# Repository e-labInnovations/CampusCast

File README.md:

<p align="center">
  
</p>

<p align="justify">
CampusCast is an IoT-based announcement system designed to improve communication within academic institutions. The system consists of hardware and software components, including a microcontroller, digital-to-analogue converter, power amplifier, acknowledgement button, backend IoT server, WebSocket technology, and mobile app. With CampusCast, teachers and authorities can send voice announcements with customizable routes to specific classrooms, branches, years, or classes, ensuring every message is received and acknowledged. The system also includes features such as Smart Notifications and Exam Time Alerts to provide targeted and timely communication without disrupting class activities. CampusCast aims to modernize the communication system in colleges and universities, enhance the campus experience for everyone involved, and improve student engagement and academic success.
</p>

- [CampusCast Mobile APP](https://github.com/e-labInnovations/CampusCast-app)
- [CampusCast Server](https://github.com/e-labInnovations/CampusCast-server)

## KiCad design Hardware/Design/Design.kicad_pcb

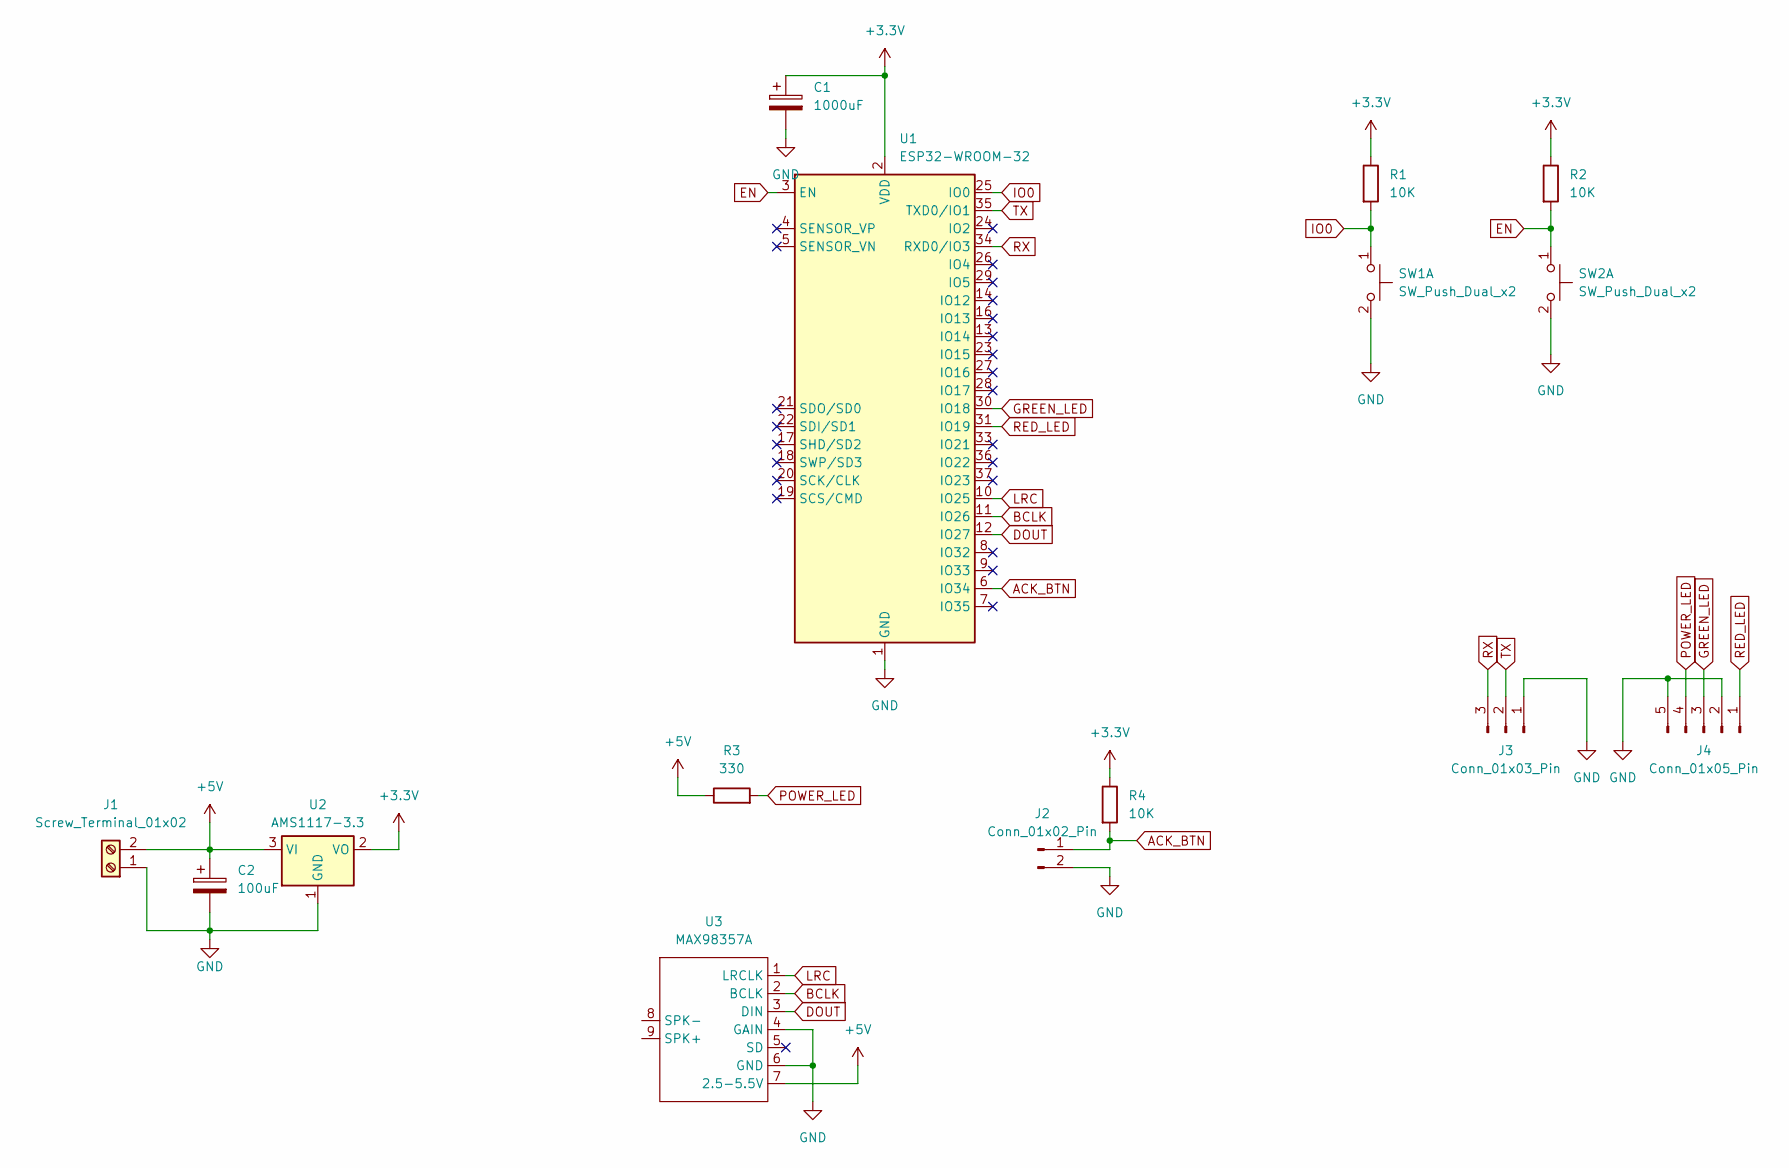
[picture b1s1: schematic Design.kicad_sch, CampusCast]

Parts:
C1: 1000uF; CP_Radial_D8.0mm_P5.00mm
C2: 100uF; CP_Radial_D5.0mm_P2.00mm
J1: Screw_Terminal_01x02; TerminalBlock_Phoenix_MKDS-1,5-2-5.08_1x02_P5.08mm_Horizont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
J2: Conn_01x02_Pin; PinHeader_1x02_P2.54mm_Vertical
J3: Conn_01x03_Pin; PinHeader_1x03_P2.54mm_Vertical
J4: Conn_01x05_Pin; PinHeader_1x05_P2.54mm_Vertical
R1, R2, R4: 10K; R_Axial_DIN0207_L6.3mm_D2.5mm_P7.62mm_Horizontal
R3: 330; R_Axial_DIN0207_L6.3mm_D2.5mm_P7.62mm_Horizontal
SW1, SW2: SW_Push_Dual_x2; SW_PUSH_6mm_H7.3mm
U1: ESP32-WROOM-32; ESP32-WROOM-32_MOD
U2: AMS1117-3.3; SOT-223-3_TabPin2
U3: MAX98357A

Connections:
+3.3V: C1.1, R1.1, R2.1, R4.1, U1.2 (VDD), U2.2 (VO)
+5V: C2.1, J1.2, R3.1, U2.3 (VI), U3.7 (2.5-5.5V)
ACK_BTN: J2.1, R4.2, U1.6 (IO34)
BCLK: U1.11 (IO26), U3.2 (BCLK)
DOUT: U1.12 (IO27), U3.3 (DIN)
EN: R2.2, SW2.1 (C), U1.3 (EN)
GND: C1.2, C2.2, J1.1, J2.2, J3.1, J4.2, J4.5, SW1.2 (D), SW2.2 (D), U1.1 (GND), U1.15 (GND), U1.38 (GND), U1.39 (GND), U2.1 (GND), U3.4 (GAIN), U3.6 (GND)
GREEN_LED: J4.3, U1.30 (IO18)
IO0: R1.2, SW1.1 (C), U1.25 (IO0)
LRC: U1.10 (IO25), U3.1 (LRCLK)
POWER_LED: J4.4, R3.2
RED_LED: J4.1, U1.31 (IO19)
RX: J3.3, U1.34 (RXD0/IO3)
TX: J3.2, U1.35 (TXD0/IO1)

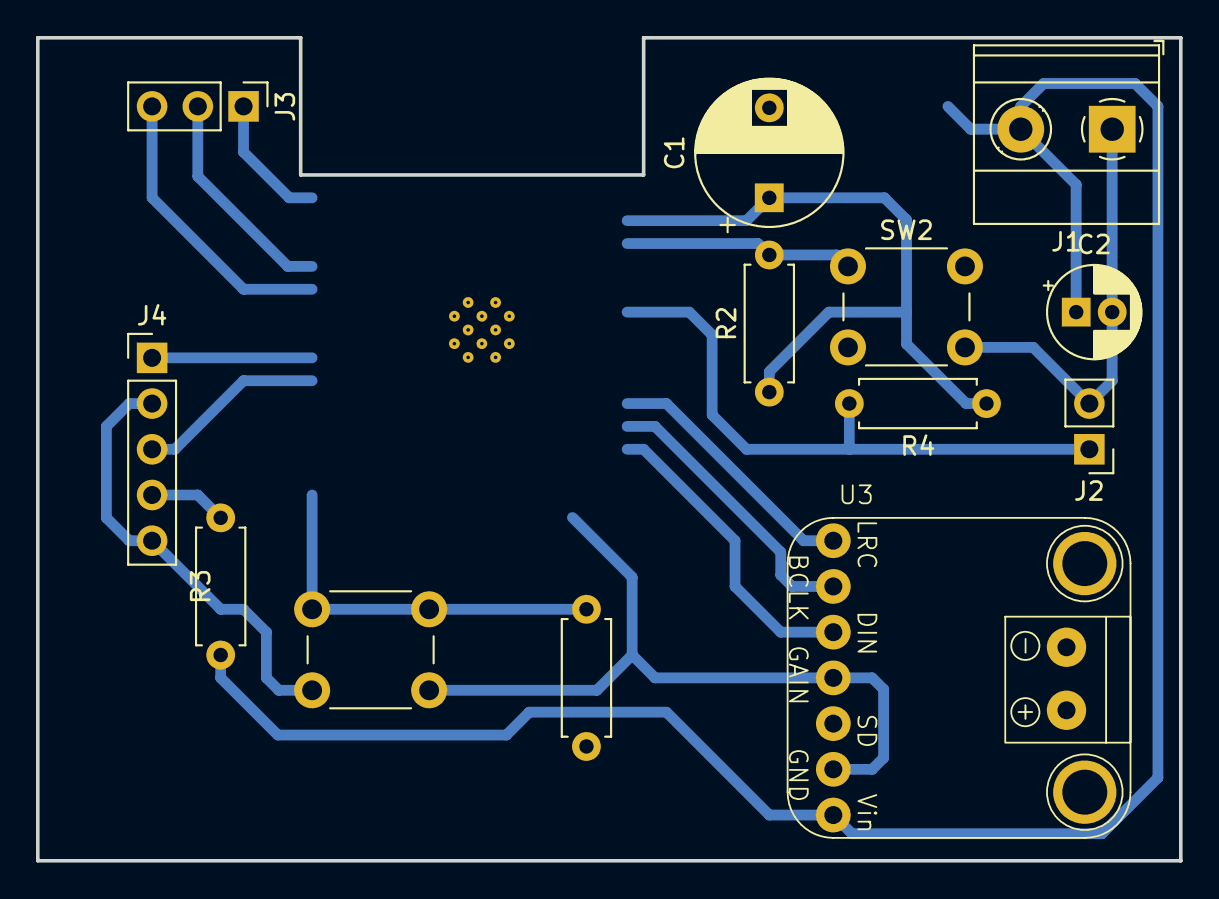
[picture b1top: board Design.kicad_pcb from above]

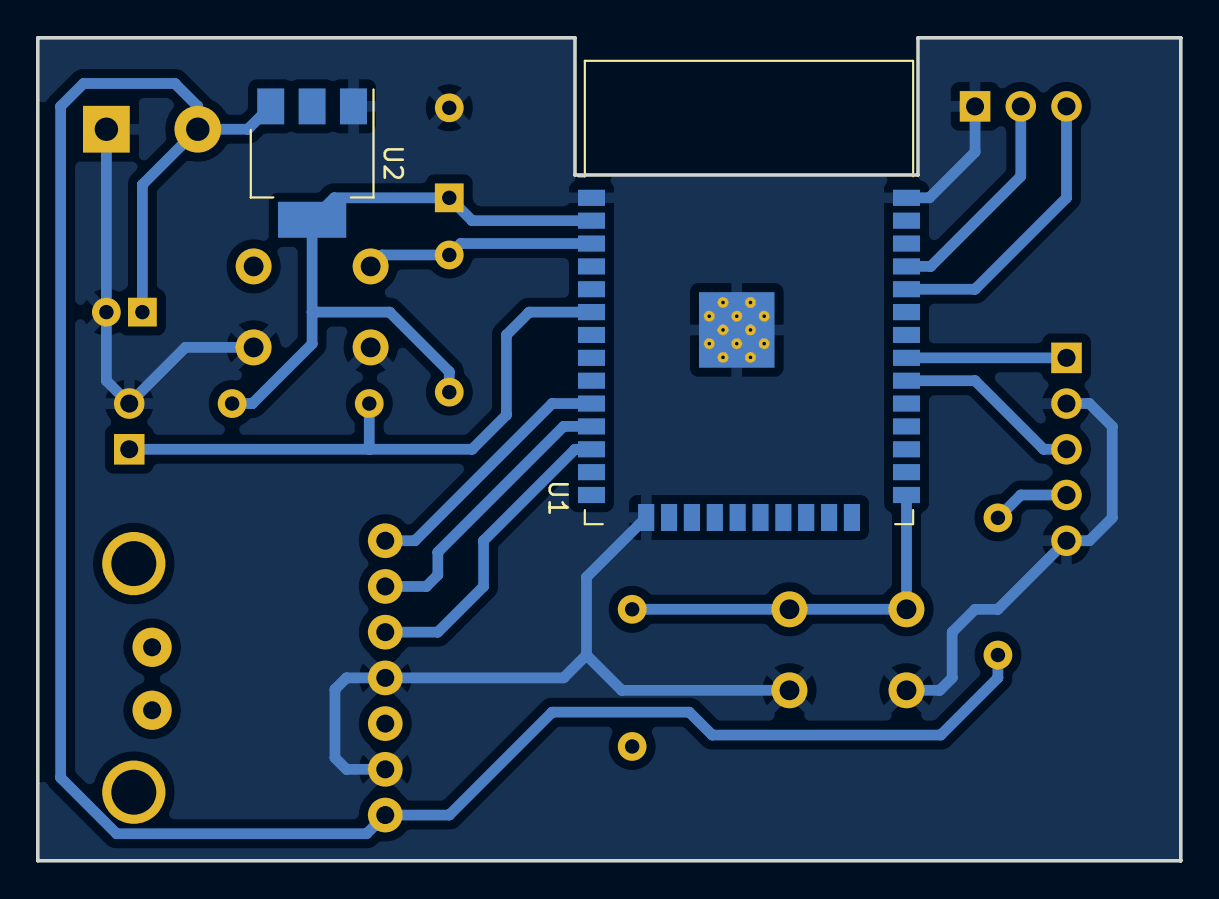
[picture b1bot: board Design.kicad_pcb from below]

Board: 2 copper layers, 63.5 x 45.7 mm, 15 parts (2 on the bottom side), 14 nets.

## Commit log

2023-03-12 logo & 1st presentation ppt
2023-03-12 svg logo added on readme
2023-04-17 New ESP32 code added
2023-04-17 main code started with classroom data
2023-04-23 Readme updated
2023-04-23 img align issue solved
2023-04-23 align="justify"
2023-06-04 Websocket added
2023-06-04 Audio test
2023-06-04 Sending connected data to server
2023-06-04 PCB Design added
2023-06-14 server configuration added
2023-06-17 3d View updated
2023-06-17 New test
2023-06-17 now h/w can receive announcements
2023-06-17 pins changed for CampusCast hardware
2023-06-17 working on CampusCast hardware
2023-06-17 M4A audio bug and connecttoserver stuck fixed
2023-06-17 ACK feature implimented
2023-06-18 only play right announcement, status led starting
2023-06-24 Hardware box stickers added
2023-06-24 Exam Schedule feature added
2023-06-24 Dynamic intro and outro
2023-06-24 Config Web Portel logo added
2023-06-24 status indicator almost completed
2024-04-27 Versions details added
